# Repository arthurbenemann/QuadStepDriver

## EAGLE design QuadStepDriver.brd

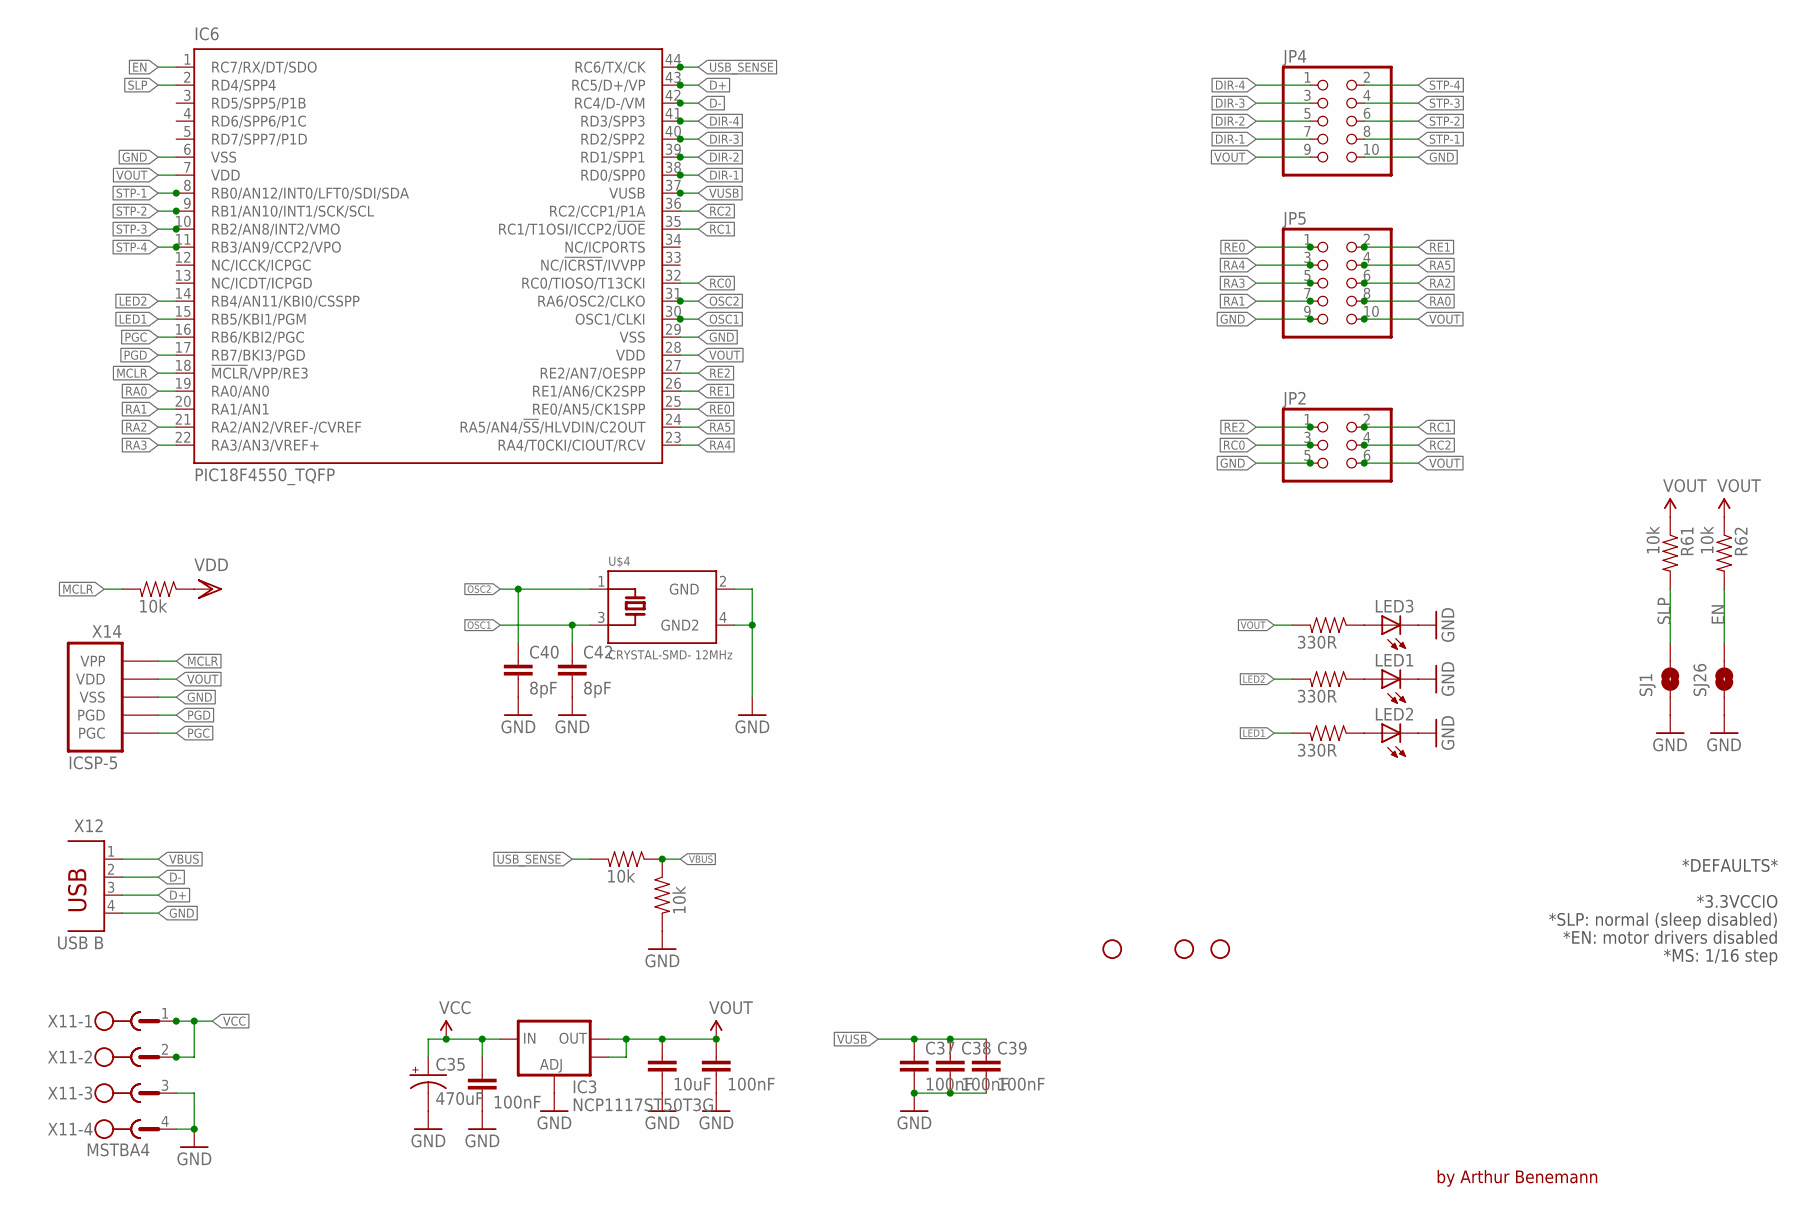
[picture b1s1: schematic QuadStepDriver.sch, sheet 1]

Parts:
C33: 10uF; 0805
C34, C36, C37, C38, C39: 100nF; 0805
C35: 470uF; PANASONIC_G
C40, C42: 8pF; 0603-CAP
IC3: NCP1117ST50T3G; SOT223
IC6: PIC18F4550_TQFP; TQFP44
JP2: PINHD-2X3; 2X03
JP4, JP5: PINHD-2X5; 2X05
JP9, JP10, JP12: STAND-OFF
LED1, LED2, LED3: LEDCHIPLED_0805; CHIPLED_0805
R33, R34, R35: 330R; 0805
R49, R50, R51: 10k; 0805
R61, R62: 10k; 0603-RES
SJ1, SJ26: SOLDERJUMPERNO; SJ_2S-NO
U$4: CRYSTAL-SMD- 12MHz; CRYSTAL-SMD-3.2X2.5
X11: MSTBA4
X12: USB B; PN61729
X14: ICSP-5; M05

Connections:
!MCLR: IC6.18 (!MCLR!/VPP/RE3), R51.2, X14.1 (VPP)
D+: IC6.43 (RC5/D+/VP), X12.3
D-: IC6.42 (RC4/D-/VM), X12.2
DIR-1: IC6.38 (RD0/SPP0), JP4.7; also elsewhere on the board
DIR-2: IC6.39 (RD1/SPP1), JP4.5; also elsewhere on the board
DIR-3: IC6.40 (RD2/SPP2), JP4.3; also elsewhere on the board
DIR-4: IC6.41 (RD3/SPP3), JP4.1; also elsewhere on the board
EN: IC6.1 (RC7/RX/DT/SDO), R62.2, SJ26.2; also elsewhere on the board
GND: C33.1, C34.1, C35.-, C36.1, C37.2, C38.2, C39.2, C40.2, C42.2, IC3.1 (ADJ), IC6.6 (VSS), IC6.29 (VSS), JP2.5, JP4.10, JP5.9, LED1.C, LED2.C, LED3.C, R50.2, SJ1.1, SJ26.1, U$4.2 (GND), U$4.4 (GND2), X11.3, X11.4, X12.4, X14.3 (VSS); also elsewhere on the board
LED1: IC6.15 (RB5/KBI1/PGM), R34.2
LED2: IC6.14 (RB4/AN11/KBI0/CSSPP), R33.2
unnamed: LED3.A, R35.1
unnamed: LED1.A, R33.1
unnamed: LED2.A, R34.1
OSC1: C42.1, IC6.30 (OSC1/CLKI), U$4.3 (OSC2)
OSC2: C40.1, IC6.31 (RA6/OSC2/CLKO), U$4.1 (OSC1)
PGC: IC6.16 (RB6/KBI2/PGC), X14.5 (PGC)
PGD: IC6.17 (RB7/BKI3/PGD), X14.4 (PGD)
RA0: IC6.19 (RA0/AN0), JP5.8
RA1: IC6.20 (RA1/AN1), JP5.7
RA2: IC6.21 (RA2/AN2/VREF-/CVREF), JP5.6
RA3: IC6.22 (RA3/AN3/VREF+), JP5.5
RA4: IC6.23 (RA4/T0CKI/CIOUT/RCV), JP5.3
RA5: IC6.24 (RA5/AN4/!SS!/HLVDIN/C2OUT), JP5.4
RC0: IC6.32 (RC0/TIOSO/T13CKI), JP2.3
RC1: IC6.35 (RC1/T1OSI/ICCP2/!UOE), JP2.2
RC2: IC6.36 (RC2/CCP1/P1A), JP2.4
RE0: IC6.25 (RE0/AN5/CK1SPP), JP5.1
RE1: IC6.26 (RE1/AN6/CK2SPP), JP5.2
RE2: IC6.27 (RE2/AN7/OESPP), JP2.1
SLP: IC6.2 (RD4/SPP4), R61.2, SJ1.2; also elsewhere on the board
STP-1: IC6.8 (RB0/AN12/INT0/LFT0/SDI/SDA), JP4.8; also elsewhere on the board
STP-2: IC6.9 (RB1/AN10/INT1/SCK/SCL), JP4.6; also elsewhere on the board
STP-3: IC6.10 (RB2/AN8/INT2/VMO), JP4.4; also elsewhere on the board
STP-4: IC6.11 (RB3/AN9/CCP2/VPO), JP4.2; also elsewhere on the board
USB_SENSE: IC6.44 (RC6/TX/CK), R49.2
VBUS: R49.1, R50.1, X12.1
VCC: C35.+, C36.2, IC3.3 (IN), X11.1, X11.2; also elsewhere on the board
VOUT: C33.2, C34.2, IC3.2 (OUT), IC3.4 (OUT), IC6.7 (VDD), IC6.28 (VDD), JP2.6, JP4.9, JP5.10, R35.2, R51.1, R61.1, R62.1, X14.2 (VDD); also elsewhere on the board
VUSB: C37.1, C38.1, C39.1, IC6.37 (VUSB)

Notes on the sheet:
*DEFAULTS*
*MS: 1/16 step
*3.3VCCIO
*EN: motor drivers disabled
*SLP: normal (sleep disabled)
by Arthur Benemann

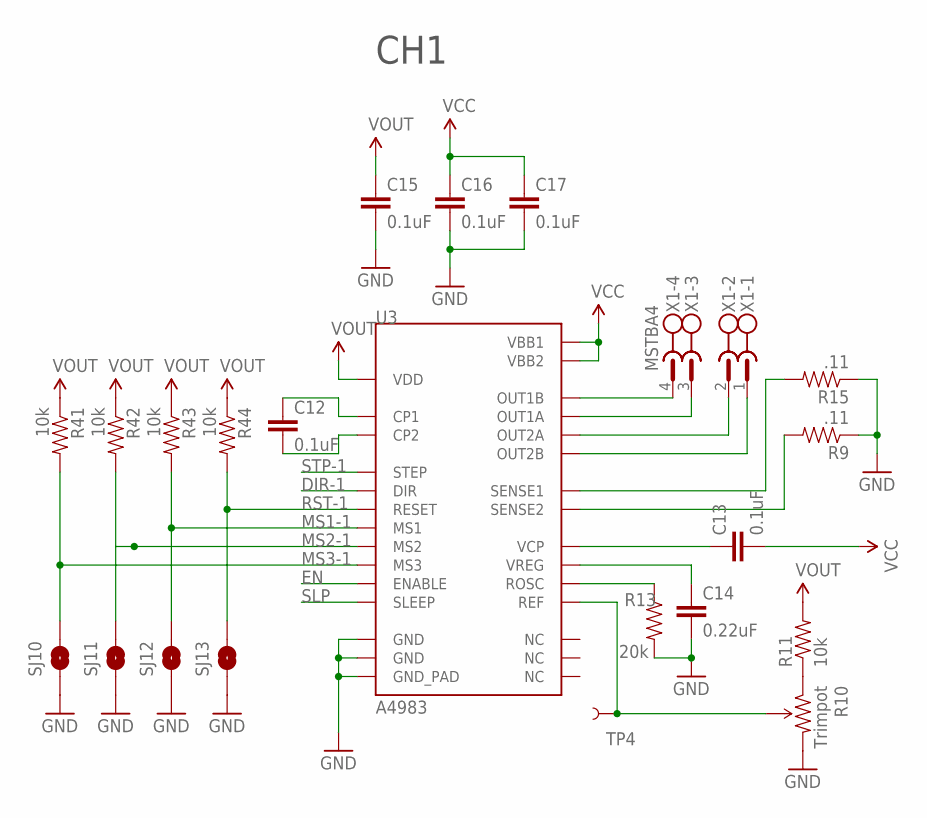
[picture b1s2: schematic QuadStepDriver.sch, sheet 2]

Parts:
C12, C13, C15, C16, C17: 0.1uF; 0603-CAP
C14: 0.22uF; 0603-CAP
R9, R15: .11; R2010
R10: Trimpot; TRIMPOT-3MM
R11, R41, R42, R43, R44: 10k; 0603-RES
R13: 20k; 0603-RES
SJ10, SJ11, SJ12, SJ13: SOLDERJUMPERNO; SJ_2S-NO
TP4: TEST-POINT3X5; PAD.03X.05
U3: A4983; QFN-28-5MM
X1: MSTBA4; MPN 1757268

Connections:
DIR-1: U3.P$19 (DIR); also elsewhere on the board
EN: U3.P$2 (ENABLE); also elsewhere on the board
GND: C14.2, C15.2, C16.2, C17.2, R9.1, R10.3 (CW), R13.2, R15.1, SJ10.1, SJ11.1, SJ12.1, SJ13.1, U3.P$3 (GND), U3.P$18 (GND), U3.P$29 (GND_PAD); also elsewhere on the board
MS1-1: R43.2, SJ12.2, U3.P$9 (MS1)
MS2-1: R42.2, SJ11.2, U3.P$10 (MS2)
MS3-1: R41.2, SJ10.2, U3.P$11 (MS3)
unnamed: R9.2, U3.P$27 (SENSE2)
unnamed: R15.2, U3.P$23 (SENSE1)
unnamed: R10.1 (CCW), R11.1
unnamed: C13.1, U3.P$6 (VCP)
unnamed: C14.1, U3.P$8 (VREG)
unnamed: R13.1, U3.P$13 (ROSC)
unnamed: R10.2 (WIPER), TP4.P$1, U3.P$17 (REF)
unnamed: C12.1, U3.P$4 (CP1)
unnamed: C12.2, U3.P$5 (CP2)
unnamed: U3.P$21 (OUT1B), X1.4
unnamed: U3.P$24 (OUT1A), X1.3
unnamed: U3.P$26 (OUT2A), X1.2
unnamed: U3.P$1 (OUT2B), X1.1
RST-1: R44.2, SJ13.2, U3.P$12 (RESET)
SLP: U3.P$14 (SLEEP); also elsewhere on the board
STP-1: U3.P$16 (STEP); also elsewhere on the board
VCC: C13.2, C16.1, C17.1, U3.P$22 (VBB1), U3.P$28 (VBB2); also elsewhere on the board
VOUT: C15.1, R11.2, R41.1, R42.1, R43.1, R44.1, U3.P$15 (VDD); also elsewhere on the board

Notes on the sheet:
CH1

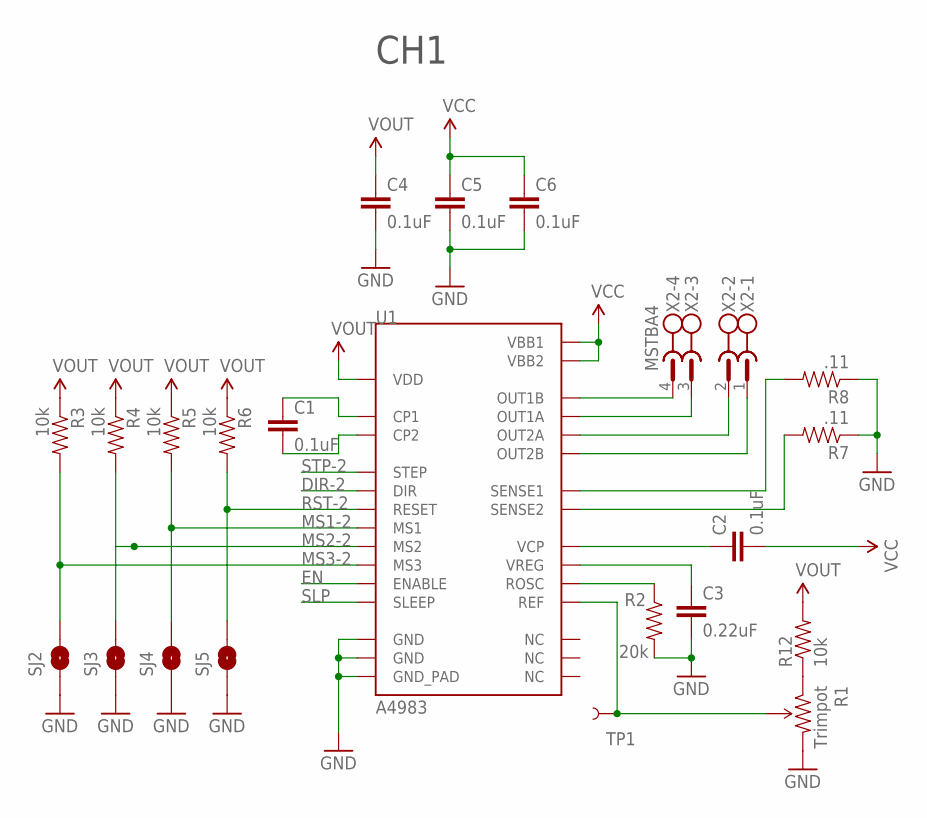
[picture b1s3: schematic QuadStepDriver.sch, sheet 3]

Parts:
C1, C2, C4, C5, C6: 0.1uF; 0603-CAP
C3: 0.22uF; 0603-CAP
R1: Trimpot; TRIMPOT-3MM
R2: 20k; 0603-RES
R3, R4, R5, R6, R12: 10k; 0603-RES
R7, R8: .11; R2010
SJ2, SJ3, SJ4, SJ5: SOLDERJUMPERNO; SJ_2S-NO
TP1: TEST-POINT3X5; PAD.03X.05
U1: A4983; QFN-28-5MM
X2: MSTBA4; MPN 1757268

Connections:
DIR-2: U1.P$19 (DIR); also elsewhere on the board
EN: U1.P$2 (ENABLE); also elsewhere on the board
GND: C3.2, C4.2, C5.2, C6.2, R1.3 (CW), R2.2, R7.1, R8.1, SJ2.1, SJ3.1, SJ4.1, SJ5.1, U1.P$3 (GND), U1.P$18 (GND), U1.P$29 (GND_PAD); also elsewhere on the board
MS1-2: R5.2, SJ4.2, U1.P$9 (MS1)
MS2-2: R4.2, SJ3.2, U1.P$10 (MS2)
MS3-2: R3.2, SJ2.2, U1.P$11 (MS3)
unnamed: C2.1, U1.P$6 (VCP)
unnamed: C3.1, U1.P$8 (VREG)
unnamed: R2.1, U1.P$13 (ROSC)
unnamed: R1.2 (WIPER), TP1.P$1, U1.P$17 (REF)
unnamed: C1.1, U1.P$4 (CP1)
unnamed: C1.2, U1.P$5 (CP2)
unnamed: U1.P$24 (OUT1A), X2.3
unnamed: U1.P$26 (OUT2A), X2.2
unnamed: U1.P$1 (OUT2B), X2.1
unnamed: U1.P$21 (OUT1B), X2.4
unnamed: R7.2, U1.P$27 (SENSE2)
unnamed: R8.2, U1.P$23 (SENSE1)
unnamed: R1.1 (CCW), R12.1
RST-2: R6.2, SJ5.2, U1.P$12 (RESET)
SLP: U1.P$14 (SLEEP); also elsewhere on the board
STP-2: U1.P$16 (STEP); also elsewhere on the board
VCC: C2.2, C5.1, C6.1, U1.P$22 (VBB1), U1.P$28 (VBB2); also elsewhere on the board
VOUT: C4.1, R3.1, R4.1, R5.1, R6.1, R12.2, U1.P$15 (VDD); also elsewhere on the board

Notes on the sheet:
CH1

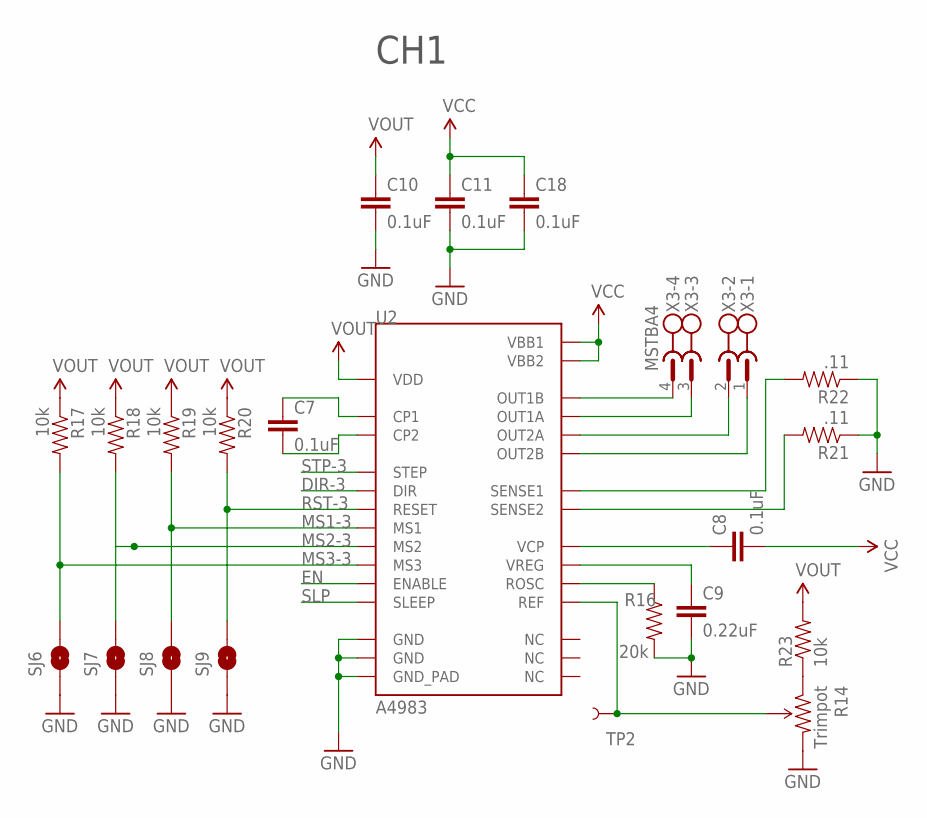
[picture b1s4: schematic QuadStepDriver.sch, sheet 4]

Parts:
C7, C8, C10, C11, C18: 0.1uF; 0603-CAP
C9: 0.22uF; 0603-CAP
R14: Trimpot; TRIMPOT-3MM
R16: 20k; 0603-RES
R17, R18, R19, R20, R23: 10k; 0603-RES
R21, R22: .11; R2010
SJ6, SJ7, SJ8, SJ9: SOLDERJUMPERNO; SJ_2S-NO
TP2: TEST-POINT3X5; PAD.03X.05
U2: A4983; QFN-28-5MM
X3: MSTBA4; MPN 1757268

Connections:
DIR-3: U2.P$19 (DIR); also elsewhere on the board
EN: U2.P$2 (ENABLE); also elsewhere on the board
GND: C9.2, C10.2, C11.2, C18.2, R14.3 (CW), R16.2, R21.1, R22.1, SJ6.1, SJ7.1, SJ8.1, SJ9.1, U2.P$3 (GND), U2.P$18 (GND), U2.P$29 (GND_PAD); also elsewhere on the board
MS1-3: R19.2, SJ8.2, U2.P$9 (MS1)
MS2-3: R18.2, SJ7.2, U2.P$10 (MS2)
MS3-3: R17.2, SJ6.2, U2.P$11 (MS3)
unnamed: C8.1, U2.P$6 (VCP)
unnamed: C9.1, U2.P$8 (VREG)
unnamed: R16.1, U2.P$13 (ROSC)
unnamed: R14.2 (WIPER), TP2.P$1, U2.P$17 (REF)
unnamed: C7.1, U2.P$4 (CP1)
unnamed: C7.2, U2.P$5 (CP2)
unnamed: U2.P$24 (OUT1A), X3.3
unnamed: U2.P$26 (OUT2A), X3.2
unnamed: U2.P$1 (OUT2B), X3.1
unnamed: U2.P$21 (OUT1B), X3.4
unnamed: R21.2, U2.P$27 (SENSE2)
unnamed: R22.2, U2.P$23 (SENSE1)
unnamed: R14.1 (CCW), R23.1
RST-3: R20.2, SJ9.2, U2.P$12 (RESET)
SLP: U2.P$14 (SLEEP); also elsewhere on the board
STP-3: U2.P$16 (STEP); also elsewhere on the board
VCC: C8.2, C11.1, C18.1, U2.P$22 (VBB1), U2.P$28 (VBB2); also elsewhere on the board
VOUT: C10.1, R17.1, R18.1, R19.1, R20.1, R23.2, U2.P$15 (VDD); also elsewhere on the board

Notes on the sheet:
CH1

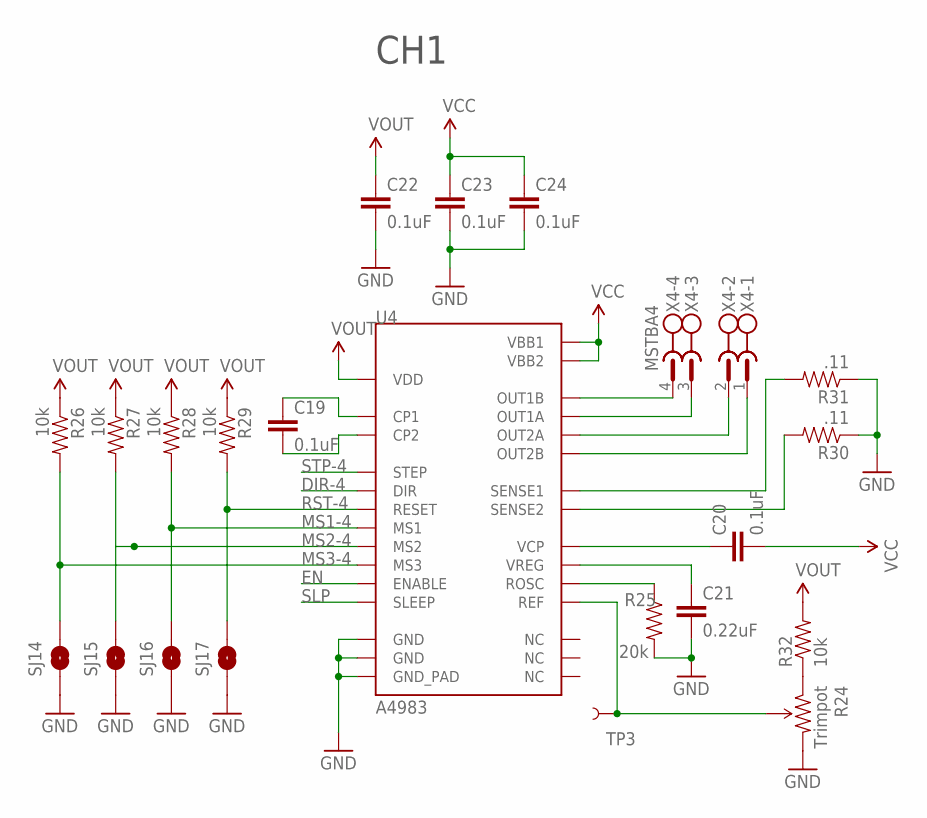
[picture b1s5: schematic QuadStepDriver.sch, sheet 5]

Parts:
C19, C20, C22, C23, C24: 0.1uF; 0603-CAP
C21: 0.22uF; 0603-CAP
R24: Trimpot; TRIMPOT-3MM
R25: 20k; 0603-RES
R26, R27, R28, R29, R32: 10k; 0603-RES
R30, R31: .11; R2010
SJ14, SJ15, SJ16, SJ17: SOLDERJUMPERNO; SJ_2S-NO
TP3: TEST-POINT3X5; PAD.03X.05
U4: A4983; QFN-28-5MM
X4: MSTBA4; MPN 1757268

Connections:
DIR-4: U4.P$19 (DIR); also elsewhere on the board
EN: U4.P$2 (ENABLE); also elsewhere on the board
GND: C21.2, C22.2, C23.2, C24.2, R24.3 (CW), R25.2, R30.1, R31.1, SJ14.1, SJ15.1, SJ16.1, SJ17.1, U4.P$3 (GND), U4.P$18 (GND), U4.P$29 (GND_PAD); also elsewhere on the board
MS1-4: R28.2, SJ16.2, U4.P$9 (MS1)
MS2-4: R27.2, SJ15.2, U4.P$10 (MS2)
MS3-4: R26.2, SJ14.2, U4.P$11 (MS3)
unnamed: C20.1, U4.P$6 (VCP)
unnamed: C21.1, U4.P$8 (VREG)
unnamed: R25.1, U4.P$13 (ROSC)
unnamed: R24.2 (WIPER), TP3.P$1, U4.P$17 (REF)
unnamed: C19.1, U4.P$4 (CP1)
unnamed: C19.2, U4.P$5 (CP2)
unnamed: U4.P$24 (OUT1A), X4.3
unnamed: U4.P$26 (OUT2A), X4.2
unnamed: U4.P$1 (OUT2B), X4.1
unnamed: U4.P$21 (OUT1B), X4.4
unnamed: R30.2, U4.P$27 (SENSE2)
unnamed: R31.2, U4.P$23 (SENSE1)
unnamed: R24.1 (CCW), R32.1
RST-4: R29.2, SJ17.2, U4.P$12 (RESET)
SLP: U4.P$14 (SLEEP); also elsewhere on the board
STP-4: U4.P$16 (STEP); also elsewhere on the board
VCC: C20.2, C23.1, C24.1, U4.P$22 (VBB1), U4.P$28 (VBB2); also elsewhere on the board
VOUT: C22.1, R26.1, R27.1, R28.1, R29.1, R32.2, U4.P$15 (VDD); also elsewhere on the board

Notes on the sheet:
CH1

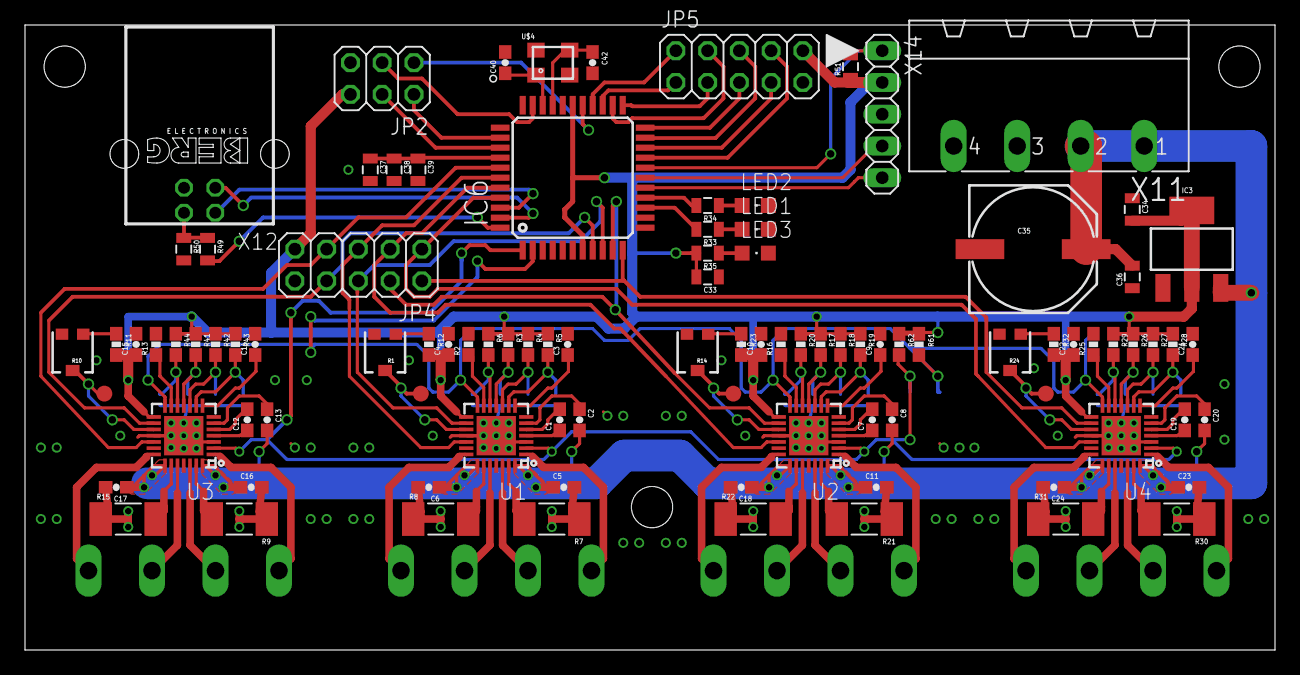
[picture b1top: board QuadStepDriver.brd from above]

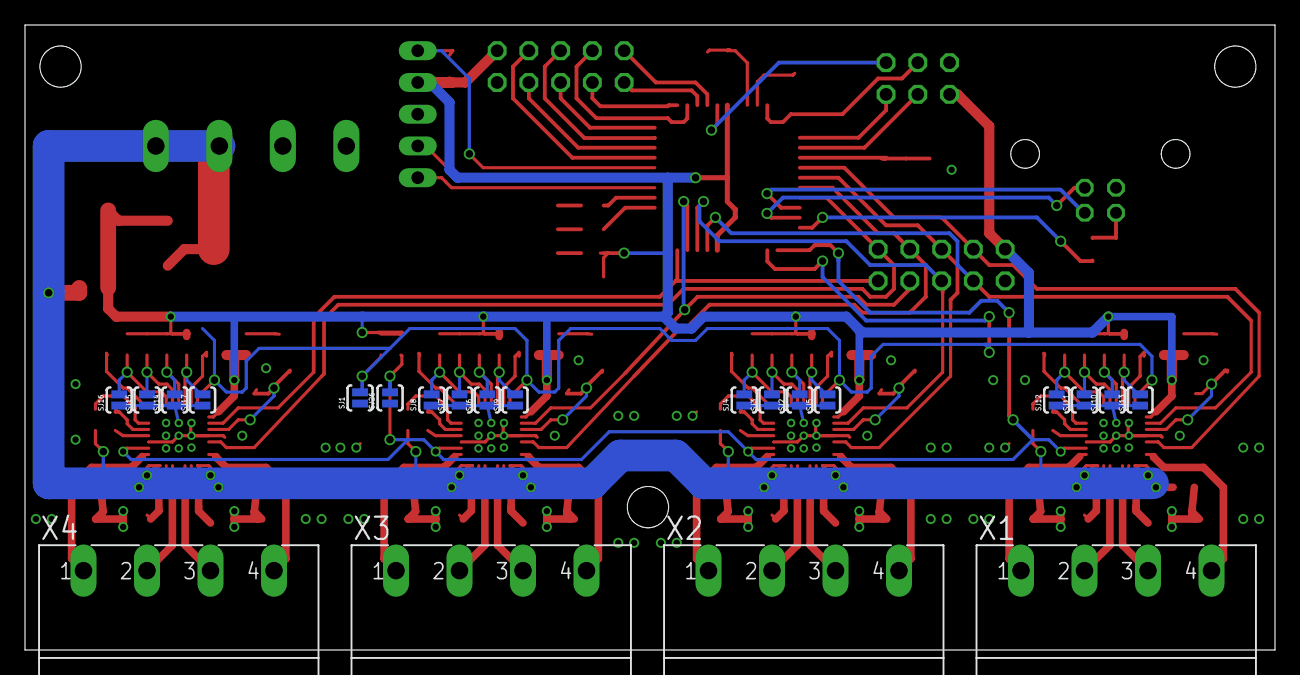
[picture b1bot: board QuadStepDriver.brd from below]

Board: 2 copper layers, 100.0 x 50.0 mm, 122 parts (22 on the bottom side), 108 nets.

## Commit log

2013-05-24 Adding some already designed boards
2013-05-24 Finished layout of one quadrant of the board (CH3).
2013-05-24 Clean-up of the layout.
2013-05-24 Layout copied to the other three quadrants.
2013-05-24 Adding a uC with USB
2013-05-25 Improving the layout
2013-05-25 Layout ....
2013-05-31 Layout with new TQFP IC
2013-05-31 Deleting unused files.
2013-05-31 Renaming files
2013-05-31 Just cleaning up the schematic
2013-06-06 PCB: Finalizando Gerbers
2013-06-29 Changing some components values, and organizing component values placement
2013-06-29 Fixing some unconneted routes from board REV1.
    PGC and power input GND are now connected.
2013-07-01 Code: Adding just enought code to make the motors spin.
